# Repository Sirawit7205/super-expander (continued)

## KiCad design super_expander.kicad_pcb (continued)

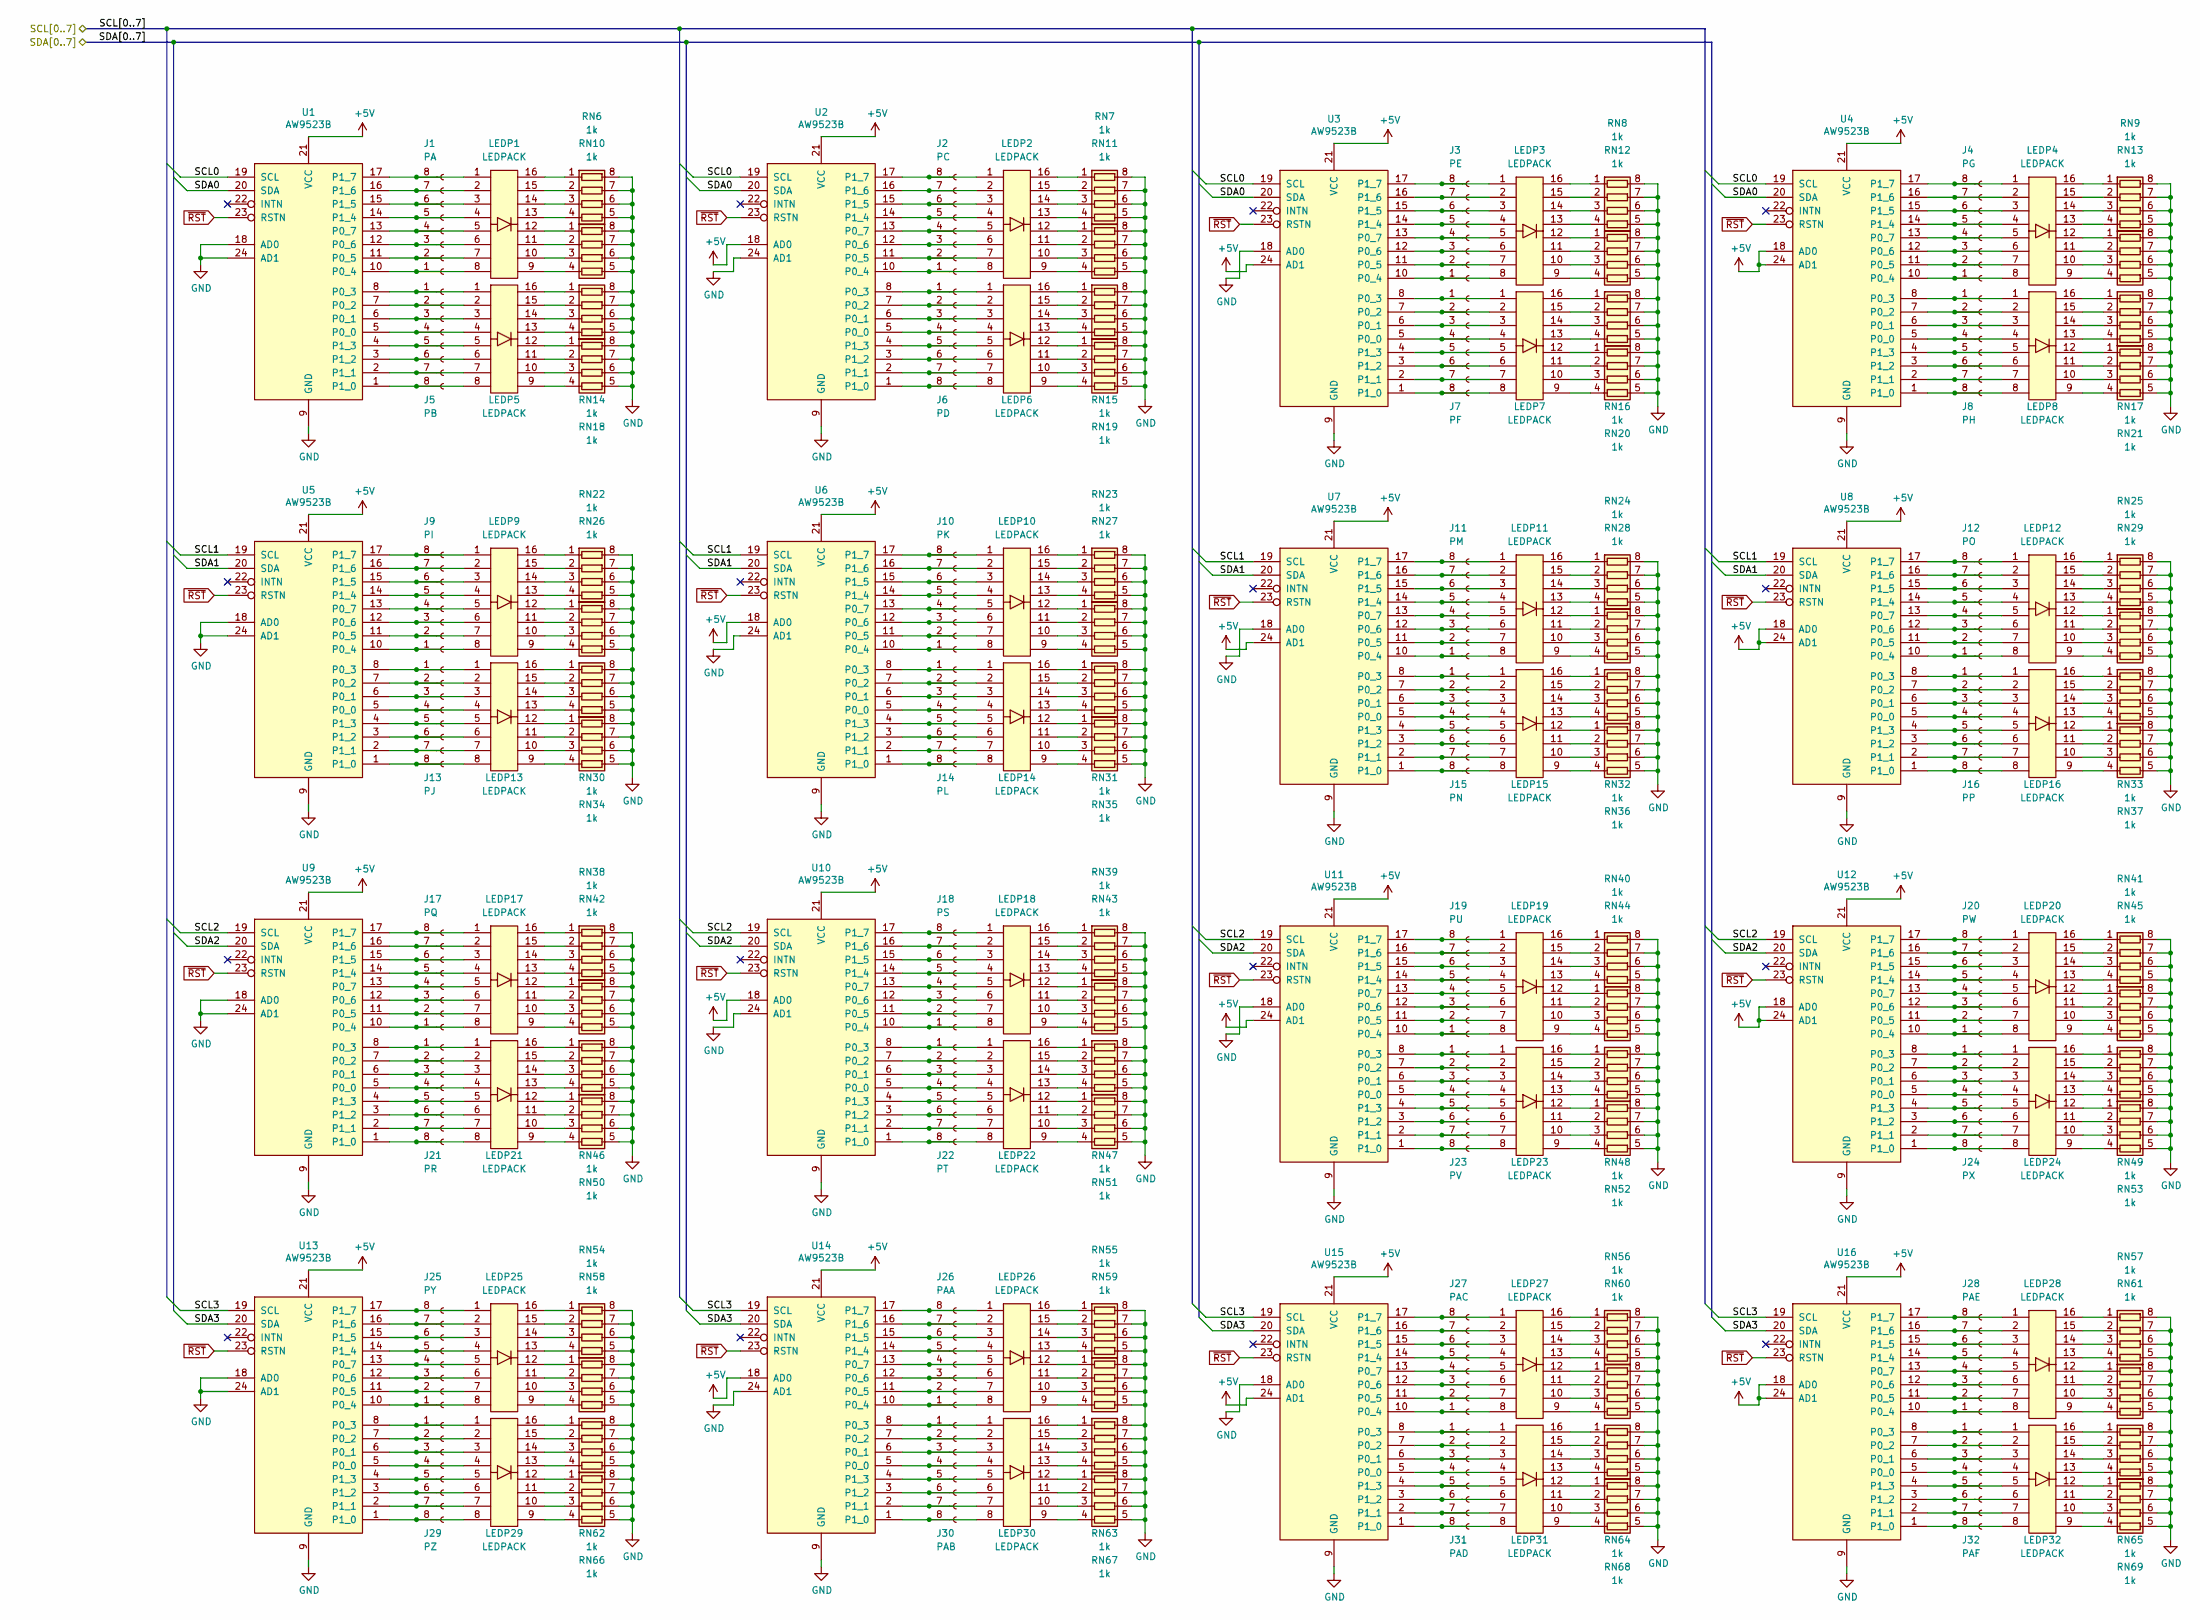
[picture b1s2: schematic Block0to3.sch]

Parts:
J1: PA; PinHeader_1x08_P1.27mm_Vertical
J2: PC; PinHeader_1x08_P1.27mm_Vertical
J3: PE; PinHeader_1x08_P1.27mm_Vertical
J4: PG; PinHeader_1x08_P1.27mm_Vertical
J5: PB; PinHeader_1x08_P1.27mm_Vertical
J6: PD; PinHeader_1x08_P1.27mm_Vertical
J7: PF; PinHeader_1x08_P1.27mm_Vertical
J8: PH; PinHeader_1x08_P1.27mm_Vertical
J9: PI; PinHeader_1x08_P1.27mm_Vertical
J10: PK; PinHeader_1x08_P1.27mm_Vertical
J11: PM; PinHeader_1x08_P1.27mm_Vertical
J12: PO; PinHeader_1x08_P1.27mm_Vertical
J13: PJ; PinHeader_1x08_P1.27mm_Vertical
J14: PL; PinHeader_1x08_P1.27mm_Vertical
J15: PN; PinHeader_1x08_P1.27mm_Vertical
J16: PP; PinHeader_1x08_P1.27mm_Vertical
J17: PQ; PinHeader_1x08_P1.27mm_Vertical
J18: PS; PinHeader_1x08_P1.27mm_Vertical
J19: PU; PinHeader_1x08_P1.27mm_Vertical
J20: PW; PinHeader_1x08_P1.27mm_Vertical
J21: PR; PinHeader_1x08_P1.27mm_Vertical
J22: PT; PinHeader_1x08_P1.27mm_Vertical
J23: PV; PinHeader_1x08_P1.27mm_Vertical
J24: PX; PinHeader_1x08_P1.27mm_Vertical
J25: PY; PinHeader_1x08_P1.27mm_Vertical
J26: PAA; PinHeader_1x08_P1.27mm_Vertical
J27: PAC; PinHeader_1x08_P1.27mm_Vertical
J28: PAE; PinHeader_1x08_P1.27mm_Vertical
J29: PZ; PinHeader_1x08_P1.27mm_Vertical
J30: PAB; PinHeader_1x08_P1.27mm_Vertical
J31: PAD; PinHeader_1x08_P1.27mm_Vertical
J32: PAF; PinHeader_1x08_P1.27mm_Vertical
LEDP1, LEDP2, LEDP3, LEDP4, LEDP5, LEDP6, LEDP7, LEDP8, LEDP9, LEDP10, LEDP11, LEDP12, LEDP13, LEDP14, LEDP15, LEDP16, LEDP17, LEDP18, LEDP19, LEDP20, LEDP21, LEDP22, LEDP23, LEDP24, LEDP25, LEDP26, LEDP27, LEDP28, LEDP29, LEDP30, LEDP31, LEDP32: LEDPACK; LED_PACK_8
RN6, RN7, RN8, RN9, RN10, RN11, RN12, RN13, RN14, RN15, RN16, RN17, RN18, RN19, RN20, RN21, RN22, RN23, RN24, RN25, RN26, RN27, RN28, RN29, RN30, RN31, RN32, RN33, RN34, RN35, RN36, RN37, RN38, RN39, RN40, RN41, RN42, RN43, RN44, RN45, RN46, RN47, RN48, RN49, RN50, RN51, RN52, RN53, RN54, RN55, RN56, RN57, RN58, RN59, RN60, RN61, RN62, RN63, RN64, RN65, RN66, RN67, RN68, RN69: 1k; R_Array_Convex_4x0402
U1, U2, U3, U4, U5, U6, U7, U8, U9, U10, U11, U12, U13, U14, U15, U16: AW9523B; QFN-24-1EP_4x4mm_P0.5mm_EP2.7x2.7mm_ThermalVias

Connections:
+5V: U1.21 (VCC), U2.18 (AD0), U2.21 (VCC), U3.21 (VCC), U3.24 (AD1), U4.18 (AD0), U4.21 (VCC), U4.24 (AD1), U5.21 (VCC), U6.18 (AD0), U6.21 (VCC), U7.21 (VCC), U7.24 (AD1), U8.18 (AD0), U8.21 (VCC), U8.24 (AD1), U9.21 (VCC), U10.18 (AD0), U10.21 (VCC), U11.21 (VCC), U11.24 (AD1), U12.18 (AD0), U12.21 (VCC), U12.24 (AD1), U13.21 (VCC), U14.18 (AD0), U14.21 (VCC), U15.21 (VCC), U15.24 (AD1), U16.18 (AD0), U16.21 (VCC), U16.24 (AD1); also elsewhere on the board
/SCL0: U1.19 (SCL), U2.19 (SCL), U3.19 (SCL), U4.19 (SCL); also elsewhere on the board
/SCL1: U5.19 (SCL), U6.19 (SCL), U7.19 (SCL), U8.19 (SCL); also elsewhere on the board
/SCL2: U9.19 (SCL), U10.19 (SCL), U11.19 (SCL), U12.19 (SCL); also elsewhere on the board
/SCL3: U13.19 (SCL), U14.19 (SCL), U15.19 (SCL), U16.19 (SCL); also elsewhere on the board
/SDA0: U1.20 (SDA), U2.20 (SDA), U3.20 (SDA), U4.20 (SDA); also elsewhere on the board
/SDA1: U5.20 (SDA), U6.20 (SDA), U7.20 (SDA), U8.20 (SDA); also elsewhere on the board
/SDA2: U9.20 (SDA), U10.20 (SDA), U11.20 (SDA), U12.20 (SDA); also elsewhere on the board
/SDA3: U13.20 (SDA), U14.20 (SDA), U15.20 (SDA), U16.20 (SDA); also elsewhere on the board
GND: RN6.5 (R4.2), RN6.6 (R3.2), RN6.7 (R2.2), RN6.8 (R1.2), RN7.5 (R4.2), RN7.6 (R3.2), RN7.7 (R2.2), RN7.8 (R1.2), RN8.5 (R4.2), RN8.6 (R3.2), RN8.7 (R2.2), RN8.8 (R1.2), RN9.5 (R4.2), RN9.6 (R3.2), RN9.7 (R2.2), RN9.8 (R1.2), RN10.5 (R4.2), RN10.6 (R3.2), RN10.7 (R2.2), RN10.8 (R1.2), RN11.5 (R4.2), RN11.6 (R3.2), RN11.7 (R2.2), RN11.8 (R1.2), RN12.5 (R4.2), RN12.6 (R3.2), RN12.7 (R2.2), RN12.8 (R1.2), RN13.5 (R4.2), RN13.6 (R3.2), RN13.7 (R2.2), RN13.8 (R1.2), RN14.5 (R4.2), RN14.6 (R3.2), RN14.7 (R2.2), RN14.8 (R1.2), RN15.5 (R4.2), RN15.6 (R3.2), RN15.7 (R2.2), RN15.8 (R1.2), RN16.5 (R4.2), RN16.6 (R3.2), RN16.7 (R2.2), RN16.8 (R1.2), RN17.5 (R4.2), RN17.6 (R3.2), RN17.7 (R2.2), RN17.8 (R1.2), RN18.5 (R4.2), RN18.6 (R3.2), RN18.7 (R2.2), RN18.8 (R1.2), RN19.5 (R4.2), RN19.6 (R3.2), RN19.7 (R2.2), RN19.8 (R1.2), RN20.5 (R4.2), RN20.6 (R3.2), RN20.7 (R2.2), RN20.8 (R1.2), RN21.5 (R4.2), RN21.6 (R3.2), RN21.7 (R2.2), RN21.8 (R1.2), RN22.5 (R4.2), RN22.6 (R3.2), RN22.7 (R2.2), RN22.8 (R1.2), RN23.5 (R4.2), RN23.6 (R3.2), RN23.7 (R2.2), RN23.8 (R1.2), RN24.5 (R4.2), RN24.6 (R3.2), RN24.7 (R2.2), RN24.8 (R1.2), RN25.5 (R4.2), RN25.6 (R3.2), RN25.7 (R2.2), RN25.8 (R1.2), RN26.5 (R4.2), RN26.6 (R3.2), RN26.7 (R2.2), RN26.8 (R1.2), RN27.5 (R4.2), RN27.6 (R3.2), RN27.7 (R2.2), RN27.8 (R1.2), RN28.5 (R4.2), RN28.6 (R3.2), RN28.7 (R2.2), RN28.8 (R1.2), RN29.5 (R4.2), RN29.6 (R3.2), RN29.7 (R2.2), RN29.8 (R1.2), RN30.5 (R4.2), RN30.6 (R3.2), RN30.7 (R2.2), RN30.8 (R1.2), RN31.5 (R4.2), RN31.6 (R3.2), RN31.7 (R2.2), RN31.8 (R1.2), RN32.5 (R4.2), RN32.6 (R3.2), RN32.7 (R2.2), RN32.8 (R1.2), RN33.5 (R4.2), RN33.6 (R3.2), RN33.7 (R2.2), RN33.8 (R1.2), RN34.5 (R4.2), RN34.6 (R3.2), RN34.7 (R2.2), RN34.8 (R1.2), RN35.5 (R4.2), RN35.6 (R3.2), RN35.7 (R2.2), RN35.8 (R1.2), RN36.5 (R4.2), RN36.6 (R3.2), RN36.7 (R2.2), RN36.8 (R1.2), RN37.5 (R4.2), RN37.6 (R3.2), RN37.7 (R2.2), RN37.8 (R1.2), RN38.5 (R4.2), RN38.6 (R3.2), RN38.7 (R2.2), RN38.8 (R1.2), RN39.5 (R4.2), RN39.6 (R3.2), RN39.7 (R2.2), RN39.8 (R1.2), RN40.5 (R4.2), RN40.6 (R3.2), RN40.7 (R2.2), RN40.8 (R1.2), RN41.5 (R4.2), RN41.6 (R3.2), RN41.7 (R2.2), RN41.8 (R1.2), RN42.5 (R4.2), RN42.6 (R3.2), RN42.7 (R2.2), RN42.8 (R1.2), RN43.5 (R4.2), RN43.6 (R3.2), RN43.7 (R2.2), RN43.8 (R1.2), RN44.5 (R4.2), RN44.6 (R3.2), RN44.7 (R2.2), RN44.8 (R1.2), RN45.5 (R4.2), RN45.6 (R3.2), RN45.7 (R2.2), RN45.8 (R1.2), RN46.5 (R4.2), RN46.6 (R3.2), RN46.7 (R2.2), RN46.8 (R1.2), RN47.5 (R4.2), RN47.6 (R3.2), RN47.7 (R2.2), RN47.8 (R1.2), RN48.5 (R4.2), RN48.6 (R3.2), RN48.7 (R2.2), RN48.8 (R1.2), RN49.5 (R4.2), RN49.6 (R3.2), RN49.7 (R2.2), RN49.8 (R1.2), RN50.5 (R4.2), RN50.6 (R3.2), RN50.7 (R2.2), RN50.8 (R1.2), RN51.5 (R4.2), RN51.6 (R3.2), RN51.7 (R2.2), RN51.8 (R1.2), RN52.5 (R4.2), RN52.6 (R3.2), RN52.7 (R2.2), RN52.8 (R1.2), RN53.5 (R4.2), RN53.6 (R3.2), RN53.7 (R2.2), RN53.8 (R1.2), RN54.5 (R4.2), RN54.6 (R3.2), RN54.7 (R2.2), RN54.8 (R1.2), RN55.5 (R4.2), RN55.6 (R3.2), RN55.7 (R2.2), RN55.8 (R1.2), RN56.5 (R4.2), RN56.6 (R3.2), RN56.7 (R2.2), RN56.8 (R1.2), RN57.5 (R4.2), RN57.6 (R3.2), RN57.7 (R2.2), RN57.8 (R1.2), RN58.5 (R4.2), RN58.6 (R3.2), RN58.7 (R2.2), RN58.8 (R1.2), RN59.5 (R4.2), RN59.6 (R3.2), RN59.7 (R2.2), RN59.8 (R1.2), RN60.5 (R4.2), RN60.6 (R3.2), RN60.7 (R2.2), RN60.8 (R1.2), RN61.5 (R4.2), RN61.6 (R3.2), RN61.7 (R2.2), RN61.8 (R1.2), RN62.5 (R4.2), RN62.6 (R3.2), RN62.7 (R2.2), RN62.8 (R1.2), RN63.5 (R4.2), RN63.6 (R3.2), RN63.7 (R2.2), RN63.8 (R1.2), RN64.5 (R4.2), RN64.6 (R3.2), RN64.7 (R2.2), RN64.8 (R1.2), RN65.5 (R4.2), RN65.6 (R3.2), RN65.7 (R2.2), RN65.8 (R1.2), RN66.5 (R4.2), RN66.6 (R3.2), RN66.7 (R2.2), RN66.8 (R1.2), RN67.5 (R4.2), RN67.6 (R3.2), RN67.7 (R2.2), RN67.8 (R1.2), RN68.5 (R4.2), RN68.6 (R3.2), RN68.7 (R2.2), RN68.8 (R1.2), RN69.5 (R4.2), RN69.6 (R3.2), RN69.7 (R2.2), RN69.8 (R1.2), U1.9 (GND), U1.18 (AD0), U1.24 (AD1), U1.25 (GND), U2.9 (GND), U2.24 (AD1), U2.25 (GND), U3.9 (GND), U3.18 (AD0), U3.25 (GND), U4.9 (GND), U4.25 (GND), U5.9 (GND), U5.18 (AD0), U5.24 (AD1), U5.25 (GND), U6.9 (GND), U6.24 (AD1), U6.25 (GND), U7.9 (GND), U7.18 (AD0), U7.25 (GND), U8.9 (GND), U8.25 (GND), U9.9 (GND), U9.18 (AD0), U9.24 (AD1), U9.25 (GND), U10.9 (GND), U10.24 (AD1), U10.25 (GND), U11.9 (GND), U11.18 (AD0), U11.25 (GND), U12.9 (GND), U12.25 (GND), U13.9 (GND), U13.18 (AD0), U13.24 (AD1), U13.25 (GND), U14.9 (GND), U14.24 (AD1), U14.25 (GND), U15.9 (GND), U15.18 (AD0), U15.25 (GND), U16.9 (GND), U16.25 (GND); also elsewhere on the board
unnamed: J1.1, LEDP1.8, U1.10 (P0_4)
unnamed: J1.2, LEDP1.7, U1.11 (P0_5)
unnamed: J1.3, LEDP1.6, U1.12 (P0_6)
unnamed: J1.4, LEDP1.5, U1.13 (P0_7)
unnamed: J1.5, LEDP1.4, U1.14 (P1_4)
unnamed: J1.6, LEDP1.3, U1.15 (P1_5)
unnamed: J1.7, LEDP1.2, U1.16 (P1_6)
unnamed: J1.8, LEDP1.1, U1.17 (P1_7)
unnamed: J2.1, LEDP2.8, U2.10 (P0_4)
unnamed: J2.2, LEDP2.7, U2.11 (P0_5)
unnamed: J2.3, LEDP2.6, U2.12 (P0_6)
unnamed: J2.4, LEDP2.5, U2.13 (P0_7)
unnamed: J2.5, LEDP2.4, U2.14 (P1_4)
unnamed: J2.6, LEDP2.3, U2.15 (P1_5)
unnamed: J2.7, LEDP2.2, U2.16 (P1_6)
unnamed: J2.8, LEDP2.1, U2.17 (P1_7)
unnamed: J3.1, LEDP3.8, U3.10 (P0_4)
unnamed: J3.2, LEDP3.7, U3.11 (P0_5)
unnamed: J3.3, LEDP3.6, U3.12 (P0_6)
unnamed: J3.4, LEDP3.5, U3.13 (P0_7)
unnamed: J3.5, LEDP3.4, U3.14 (P1_4)
unnamed: J3.6, LEDP3.3, U3.15 (P1_5)
unnamed: J3.7, LEDP3.2, U3.16 (P1_6)
unnamed: J3.8, LEDP3.1, U3.17 (P1_7)
unnamed: J4.1, LEDP4.8, U4.10 (P0_4)
unnamed: J4.2, LEDP4.7, U4.11 (P0_5)
unnamed: J4.3, LEDP4.6, U4.12 (P0_6)
unnamed: J4.4, LEDP4.5, U4.13 (P0_7)
unnamed: J4.5, LEDP4.4, U4.14 (P1_4)
unnamed: J4.6, LEDP4.3, U4.15 (P1_5)
unnamed: J4.7, LEDP4.2, U4.16 (P1_6)
unnamed: J4.8, LEDP4.1, U4.17 (P1_7)
unnamed: J5.1, LEDP5.1, U1.8 (P0_3)
unnamed: J5.2, LEDP5.2, U1.7 (P0_2)
unnamed: J5.3, LEDP5.3, U1.6 (P0_1)
unnamed: J5.4, LEDP5.4, U1.5 (P0_0)
unnamed: J5.5, LEDP5.5, U1.4 (P1_3)
unnamed: J5.6, LEDP5.6, U1.3 (P1_2)
unnamed: J5.7, LEDP5.7, U1.2 (P1_1)
unnamed: J5.8, LEDP5.8, U1.1 (P1_0)
unnamed: J6.1, LEDP6.1, U2.8 (P0_3)
unnamed: J6.2, LEDP6.2, U2.7 (P0_2)
unnamed: J6.3, LEDP6.3, U2.6 (P0_1)
unnamed: J6.4, LEDP6.4, U2.5 (P0_0)
unnamed: J6.5, LEDP6.5, U2.4 (P1_3)
unnamed: J6.6, LEDP6.6, U2.3 (P1_2)
unnamed: J6.7, LEDP6.7, U2.2 (P1_1)
unnamed: J6.8, LEDP6.8, U2.1 (P1_0)
unnamed: J7.1, LEDP7.1, U3.8 (P0_3)
unnamed: J7.2, LEDP7.2, U3.7 (P0_2)
unnamed: J7.3, LEDP7.3, U3.6 (P0_1)
unnamed: J7.4, LEDP7.4, U3.5 (P0_0)
unnamed: J7.5, LEDP7.5, U3.4 (P1_3)
unnamed: J7.6, LEDP7.6, U3.3 (P1_2)
unnamed: J7.7, LEDP7.7, U3.2 (P1_1)
unnamed: J7.8, LEDP7.8, U3.1 (P1_0)
unnamed: J8.1, LEDP8.1, U4.8 (P0_3)
unnamed: J8.2, LEDP8.2, U4.7 (P0_2)
unnamed: J8.3, LEDP8.3, U4.6 (P0_1)
unnamed: J8.4, LEDP8.4, U4.5 (P0_0)
unnamed: J8.5, LEDP8.5, U4.4 (P1_3)
unnamed: J8.6, LEDP8.6, U4.3 (P1_2)
unnamed: J8.7, LEDP8.7, U4.2 (P1_1)
unnamed: J8.8, LEDP8.8, U4.1 (P1_0)
unnamed: J9.1, LEDP9.8, U5.10 (P0_4)
unnamed: J9.2, LEDP9.7, U5.11 (P0_5)
unnamed: J9.3, LEDP9.6, U5.12 (P0_6)
unnamed: J9.4, LEDP9.5, U5.13 (P0_7)
unnamed: J9.5, LEDP9.4, U5.14 (P1_4)
unnamed: J9.6, LEDP9.3, U5.15 (P1_5)
unnamed: J9.7, LEDP9.2, U5.16 (P1_6)
unnamed: J9.8, LEDP9.1, U5.17 (P1_7)
unnamed: J10.1, LEDP10.8, U6.10 (P0_4)
unnamed: J10.2, LEDP10.7, U6.11 (P0_5)
unnamed: J10.3, LEDP10.6, U6.12 (P0_6)
unnamed: J10.4, LEDP10.5, U6.13 (P0_7)
unnamed: J10.5, LEDP10.4, U6.14 (P1_4)
unnamed: J10.6, LEDP10.3, U6.15 (P1_5)
unnamed: J10.7, LEDP10.2, U6.16 (P1_6)
unnamed: J10.8, LEDP10.1, U6.17 (P1_7)
unnamed: J11.1, LEDP11.8, U7.10 (P0_4)
unnamed: J11.2, LEDP11.7, U7.11 (P0_5)
unnamed: J11.3, LEDP11.6, U7.12 (P0_6)
unnamed: J11.4, LEDP11.5, U7.13 (P0_7)
unnamed: J11.5, LEDP11.4, U7.14 (P1_4)
unnamed: J11.6, LEDP11.3, U7.15 (P1_5)
unnamed: J11.7, LEDP11.2, U7.16 (P1_6)
unnamed: J11.8, LEDP11.1, U7.17 (P1_7)
unnamed: J12.1, LEDP12.8, U8.10 (P0_4)
unnamed: J12.2, LEDP12.7, U8.11 (P0_5)
unnamed: J12.3, LEDP12.6, U8.12 (P0_6)
unnamed: J12.4, LEDP12.5, U8.13 (P0_7)
unnamed: J12.5, LEDP12.4, U8.14 (P1_4)
unnamed: J12.6, LEDP12.3, U8.15 (P1_5)
unnamed: J12.7, LEDP12.2, U8.16 (P1_6)
unnamed: J12.8, LEDP12.1, U8.17 (P1_7)
unnamed: J13.1, LEDP13.1, U5.8 (P0_3)
unnamed: J13.2, LEDP13.2, U5.7 (P0_2)
unnamed: J13.3, LEDP13.3, U5.6 (P0_1)
unnamed: J13.4, LEDP13.4, U5.5 (P0_0)
unnamed: J13.5, LEDP13.5, U5.4 (P1_3)
unnamed: J13.6, LEDP13.6, U5.3 (P1_2)
unnamed: J13.7, LEDP13.7, U5.2 (P1_1)
unnamed: J13.8, LEDP13.8, U5.1 (P1_0)
unnamed: J14.1, LEDP14.1, U6.8 (P0_3)
unnamed: J14.2, LEDP14.2, U6.7 (P0_2)
unnamed: J14.3, LEDP14.3, U6.6 (P0_1)
unnamed: J14.4, LEDP14.4, U6.5 (P0_0)
unnamed: J14.5, LEDP14.5, U6.4 (P1_3)
unnamed: J14.6, LEDP14.6, U6.3 (P1_2)
unnamed: J14.7, LEDP14.7, U6.2 (P1_1)
unnamed: J14.8, LEDP14.8, U6.1 (P1_0)
unnamed: J15.1, LEDP15.1, U7.8 (P0_3)
unnamed: J15.2, LEDP15.2, U7.7 (P0_2)
unnamed: J15.3, LEDP15.3, U7.6 (P0_1)
unnamed: J15.4, LEDP15.4, U7.5 (P0_0)
unnamed: J15.5, LEDP15.5, U7.4 (P1_3)
unnamed: J15.6, LEDP15.6, U7.3 (P1_2)
unnamed: J15.7, LEDP15.7, U7.2 (P1_1)
unnamed: J15.8, LEDP15.8, U7.1 (P1_0)
unnamed: J16.1, LEDP16.1, U8.8 (P0_3)
unnamed: J16.2, LEDP16.2, U8.7 (P0_2)
unnamed: J16.3, LEDP16.3, U8.6 (P0_1)
unnamed: J16.4, LEDP16.4, U8.5 (P0_0)
unnamed: J16.5, LEDP16.5, U8.4 (P1_3)
unnamed: J16.6, LEDP16.6, U8.3 (P1_2)
unnamed: J16.7, LEDP16.7, U8.2 (P1_1)
unnamed: J16.8, LEDP16.8, U8.1 (P1_0)
unnamed: J17.1, LEDP17.8, U9.10 (P0_4)
unnamed: J17.2, LEDP17.7, U9.11 (P0_5)
unnamed: J17.3, LEDP17.6, U9.12 (P0_6)
unnamed: J17.4, LEDP17.5, U9.13 (P0_7)
unnamed: J17.5, LEDP17.4, U9.14 (P1_4)
unnamed: J17.6, LEDP17.3, U9.15 (P1_5)
unnamed: J17.7, LEDP17.2, U9.16 (P1_6)
unnamed: J17.8, LEDP17.1, U9.17 (P1_7)
unnamed: J18.1, LEDP18.8, U10.10 (P0_4)
unnamed: J18.2, LEDP18.7, U10.11 (P0_5)
unnamed: J18.3, LEDP18.6, U10.12 (P0_6)
unnamed: J18.4, LEDP18.5, U10.13 (P0_7)
unnamed: J18.5, LEDP18.4, U10.14 (P1_4)
unnamed: J18.6, LEDP18.3, U10.15 (P1_5)
unnamed: J18.7, LEDP18.2, U10.16 (P1_6)
unnamed: J18.8, LEDP18.1, U10.17 (P1_7)
unnamed: J19.1, LEDP19.8, U11.10 (P0_4)
unnamed: J19.2, LEDP19.7, U11.11 (P0_5)
unnamed: J19.3, LEDP19.6, U11.12 (P0_6)
unnamed: J19.4, LEDP19.5, U11.13 (P0_7)
unnamed: J19.5, LEDP19.4, U11.14 (P1_4)
unnamed: J19.6, LEDP19.3, U11.15 (P1_5)
unnamed: J19.7, LEDP19.2, U11.16 (P1_6)
unnamed: J19.8, LEDP19.1, U11.17 (P1_7)
unnamed: J20.1, LEDP20.8, U12.10 (P0_4)
unnamed: J20.2, LEDP20.7, U12.11 (P0_5)
unnamed: J20.3, LEDP20.6, U12.12 (P0_6)
unnamed: J20.4, LEDP20.5, U12.13 (P0_7)
unnamed: J20.5, LEDP20.4, U12.14 (P1_4)
unnamed: J20.6, LEDP20.3, U12.15 (P1_5)
unnamed: J20.7, LEDP20.2, U12.16 (P1_6)
unnamed: J20.8, LEDP20.1, U12.17 (P1_7)
unnamed: J21.1, LEDP21.1, U9.8 (P0_3)
unnamed: J21.2, LEDP21.2, U9.7 (P0_2)
unnamed: J21.3, LEDP21.3, U9.6 (P0_1)
unnamed: J21.4, LEDP21.4, U9.5 (P0_0)
unnamed: J21.5, LEDP21.5, U9.4 (P1_3)
unnamed: J21.6, LEDP21.6, U9.3 (P1_2)
unnamed: J21.7, LEDP21.7, U9.2 (P1_1)
unnamed: J21.8, LEDP21.8, U9.1 (P1_0)
unnamed: J22.1, LEDP22.1, U10.8 (P0_3)
unnamed: J22.2, LEDP22.2, U10.7 (P0_2)
unnamed: J22.3, LEDP22.3, U10.6 (P0_1)
unnamed: J22.4, LEDP22.4, U10.5 (P0_0)
unnamed: J22.5, LEDP22.5, U10.4 (P1_3)
unnamed: J22.6, LEDP22.6, U10.3 (P1_2)
unnamed: J22.7, LEDP22.7, U10.2 (P1_1)
unnamed: J22.8, LEDP22.8, U10.1 (P1_0)
unnamed: J23.1, LEDP23.1, U11.8 (P0_3)
unnamed: J23.2, LEDP23.2, U11.7 (P0_2)
unnamed: J23.3, LEDP23.3, U11.6 (P0_1)
unnamed: J23.4, LEDP23.4, U11.5 (P0_0)
unnamed: J23.5, LEDP23.5, U11.4 (P1_3)
unnamed: J23.6, LEDP23.6, U11.3 (P1_2)
unnamed: J23.7, LEDP23.7, U11.2 (P1_1)
unnamed: J23.8, LEDP23.8, U11.1 (P1_0)
unnamed: J24.1, LEDP24.1, U12.8 (P0_3)
unnamed: J24.2, LEDP24.2, U12.7 (P0_2)
unnamed: J24.3, LEDP24.3, U12.6 (P0_1)
unnamed: J24.4, LEDP24.4, U12.5 (P0_0)
unnamed: J24.5, LEDP24.5, U12.4 (P1_3)
unnamed: J24.6, LEDP24.6, U12.3 (P1_2)
unnamed: J24.7, LEDP24.7, U12.2 (P1_1)
unnamed: J24.8, LEDP24.8, U12.1 (P1_0)
unnamed: J25.1, LEDP25.8, U13.10 (P0_4)
unnamed: J25.2, LEDP25.7, U13.11 (P0_5)
unnamed: J25.3, LEDP25.6, U13.12 (P0_6)
unnamed: J25.4, LEDP25.5, U13.13 (P0_7)
unnamed: J25.5, LEDP25.4, U13.14 (P1_4)
unnamed: J25.6, LEDP25.3, U13.15 (P1_5)
unnamed: J25.7, LEDP25.2, U13.16 (P1_6)
unnamed: J25.8, LEDP25.1, U13.17 (P1_7)
unnamed: J26.1, LEDP26.8, U14.10 (P0_4)
unnamed: J26.2, LEDP26.7, U14.11 (P0_5)
unnamed: J26.3, LEDP26.6, U14.12 (P0_6)
unnamed: J26.4, LEDP26.5, U14.13 (P0_7)
unnamed: J26.5, LEDP26.4, U14.14 (P1_4)
unnamed: J26.6, LEDP26.3, U14.15 (P1_5)
unnamed: J26.7, LEDP26.2, U14.16 (P1_6)
unnamed: J26.8, LEDP26.1, U14.17 (P1_7)
unnamed: J27.1, LEDP27.8, U15.10 (P0_4)
unnamed: J27.2, LEDP27.7, U15.11 (P0_5)
unnamed: J27.3, LEDP27.6, U15.12 (P0_6)
unnamed: J27.4, LEDP27.5, U15.13 (P0_7)
unnamed: J27.5, LEDP27.4, U15.14 (P1_4)
unnamed: J27.6, LEDP27.3, U15.15 (P1_5)
unnamed: J27.7, LEDP27.2, U15.16 (P1_6)
unnamed: J27.8, LEDP27.1, U15.17 (P1_7)
unnamed: J28.1, LEDP28.8, U16.10 (P0_4)
unnamed: J28.2, LEDP28.7, U16.11 (P0_5)
unnamed: J28.3, LEDP28.6, U16.12 (P0_6)
unnamed: J28.4, LEDP28.5, U16.13 (P0_7)
unnamed: J28.5, LEDP28.4, U16.14 (P1_4)
unnamed: J28.6, LEDP28.3, U16.15 (P1_5)
unnamed: J28.7, LEDP28.2, U16.16 (P1_6)
unnamed: J28.8, LEDP28.1, U16.17 (P1_7)
unnamed: J29.1, LEDP29.1, U13.8 (P0_3)
unnamed: J29.2, LEDP29.2, U13.7 (P0_2)
unnamed: J29.3, LEDP29.3, U13.6 (P0_1)
unnamed: J29.4, LEDP29.4, U13.5 (P0_0)
unnamed: J29.5, LEDP29.5, U13.4 (P1_3)
unnamed: J29.6, LEDP29.6, U13.3 (P1_2)
unnamed: J29.7, LEDP29.7, U13.2 (P1_1)
unnamed: J29.8, LEDP29.8, U13.1 (P1_0)
unnamed: J30.1, LEDP30.1, U14.8 (P0_3)
unnamed: J30.2, LEDP30.2, U14.7 (P0_2)
unnamed: J30.3, LEDP30.3, U14.6 (P0_1)
unnamed: J30.4, LEDP30.4, U14.5 (P0_0)
unnamed: J30.5, LEDP30.5, U14.4 (P1_3)
unnamed: J30.6, LEDP30.6, U14.3 (P1_2)
unnamed: J30.7, LEDP30.7, U14.2 (P1_1)
unnamed: J30.8, LEDP30.8, U14.1 (P1_0)
unnamed: J31.1, LEDP31.1, U15.8 (P0_3)
unnamed: J31.2, LEDP31.2, U15.7 (P0_2)
unnamed: J31.3, LEDP31.3, U15.6 (P0_1)
unnamed: J31.4, LEDP31.4, U15.5 (P0_0)
unnamed: J31.5, LEDP31.5, U15.4 (P1_3)
unnamed: J31.6, LEDP31.6, U15.3 (P1_2)
unnamed: J31.7, LEDP31.7, U15.2 (P1_1)
unnamed: J31.8, LEDP31.8, U15.1 (P1_0)
unnamed: J32.1, LEDP32.1, U16.8 (P0_3)
unnamed: J32.2, LEDP32.2, U16.7 (P0_2)
unnamed: J32.3, LEDP32.3, U16.6 (P0_1)
unnamed: J32.4, LEDP32.4, U16.5 (P0_0)
unnamed: J32.5, LEDP32.5, U16.4 (P1_3)
unnamed: J32.6, LEDP32.6, U16.3 (P1_2)
unnamed: J32.7, LEDP32.7, U16.2 (P1_1)
unnamed: J32.8, LEDP32.8, U16.1 (P1_0)
unnamed: LEDP1.9, RN10.4 (R4.1)
unnamed: LEDP1.10, RN10.3 (R3.1)
unnamed: LEDP1.11, RN10.2 (R2.1)
unnamed: LEDP1.12, RN10.1 (R1.1)
unnamed: LEDP1.13, RN6.4 (R4.1)
unnamed: LEDP1.14, RN6.3 (R3.1)
unnamed: LEDP1.15, RN6.2 (R2.1)
unnamed: LEDP1.16, RN6.1 (R1.1)
unnamed: LEDP2.9, RN11.4 (R4.1)
unnamed: LEDP2.10, RN11.3 (R3.1)
unnamed: LEDP2.11, RN11.2 (R2.1)
unnamed: LEDP2.12, RN11.1 (R1.1)
unnamed: LEDP2.13, RN7.4 (R4.1)
unnamed: LEDP2.14, RN7.3 (R3.1)
unnamed: LEDP2.15, RN7.2 (R2.1)
unnamed: LEDP2.16, RN7.1 (R1.1)
unnamed: LEDP3.9, RN12.4 (R4.1)
unnamed: LEDP3.10, RN12.3 (R3.1)
unnamed: LEDP3.11, RN12.2 (R2.1)
unnamed: LEDP3.12, RN12.1 (R1.1)
unnamed: LEDP3.13, RN8.4 (R4.1)
unnamed: LEDP3.14, RN8.3 (R3.1)
unnamed: LEDP3.15, RN8.2 (R2.1)
unnamed: LEDP3.16, RN8.1 (R1.1)
unnamed: LEDP4.9, RN13.4 (R4.1)
unnamed: LEDP4.10, RN13.3 (R3.1)
unnamed: LEDP4.11, RN13.2 (R2.1)
unnamed: LEDP4.12, RN13.1 (R1.1)
unnamed: LEDP4.13, RN9.4 (R4.1)
unnamed: LEDP4.14, RN9.3 (R3.1)
unnamed: LEDP4.15, RN9.2 (R2.1)
unnamed: LEDP4.16, RN9.1 (R1.1)
unnamed: LEDP5.9, RN18.4 (R4.1)
unnamed: LEDP5.10, RN18.3 (R3.1)
unnamed: LEDP5.11, RN18.2 (R2.1)
unnamed: LEDP5.12, RN18.1 (R1.1)
unnamed: LEDP5.13, RN14.4 (R4.1)
unnamed: LEDP5.14, RN14.3 (R3.1)
unnamed: LEDP5.15, RN14.2 (R2.1)
unnamed: LEDP5.16, RN14.1 (R1.1)
unnamed: LEDP6.9, RN19.4 (R4.1)
unnamed: LEDP6.10, RN19.3 (R3.1)
unnamed: LEDP6.11, RN19.2 (R2.1)
unnamed: LEDP6.12, RN19.1 (R1.1)
unnamed: LEDP6.13, RN15.4 (R4.1)
unnamed: LEDP6.14, RN15.3 (R3.1)
unnamed: LEDP6.15, RN15.2 (R2.1)
unnamed: LEDP6.16, RN15.1 (R1.1)
unnamed: LEDP7.9, RN20.4 (R4.1)
unnamed: LEDP7.10, RN20.3 (R3.1)
unnamed: LEDP7.11, RN20.2 (R2.1)
unnamed: LEDP7.12, RN20.1 (R1.1)
unnamed: LEDP7.13, RN16.4 (R4.1)
unnamed: LEDP7.14, RN16.3 (R3.1)
unnamed: LEDP7.15, RN16.2 (R2.1)
unnamed: LEDP7.16, RN16.1 (R1.1)
unnamed: LEDP8.9, RN21.4 (R4.1)
unnamed: LEDP8.10, RN21.3 (R3.1)
unnamed: LEDP8.11, RN21.2 (R2.1)
unnamed: LEDP8.12, RN21.1 (R1.1)
unnamed: LEDP8.13, RN17.4 (R4.1)
unnamed: LEDP8.14, RN17.3 (R3.1)
unnamed: LEDP8.15, RN17.2 (R2.1)
unnamed: LEDP8.16, RN17.1 (R1.1)
unnamed: LEDP9.9, RN26.4 (R4.1)
unnamed: LEDP9.10, RN26.3 (R3.1)
unnamed: LEDP9.11, RN26.2 (R2.1)
unnamed: LEDP9.12, RN26.1 (R1.1)
unnamed: LEDP9.13, RN22.4 (R4.1)
unnamed: LEDP9.14, RN22.3 (R3.1)
unnamed: LEDP9.15, RN22.2 (R2.1)
unnamed: LEDP9.16, RN22.1 (R1.1)
unnamed: LEDP10.9, RN27.4 (R4.1)
unnamed: LEDP10.10, RN27.3 (R3.1)
unnamed: LEDP10.11, RN27.2 (R2.1)
unnamed: LEDP10.12, RN27.1 (R1.1)
unnamed: LEDP10.13, RN23.4 (R4.1)
unnamed: LEDP10.14, RN23.3 (R3.1)
unnamed: LEDP10.15, RN23.2 (R2.1)
unnamed: LEDP10.16, RN23.1 (R1.1)
unnamed: LEDP11.9, RN28.4 (R4.1)
unnamed: LEDP11.10, RN28.3 (R3.1)
unnamed: LEDP11.11, RN28.2 (R2.1)
unnamed: LEDP11.12, RN28.1 (R1.1)
unnamed: LEDP11.13, RN24.4 (R4.1)
unnamed: LEDP11.14, RN24.3 (R3.1)
unnamed: LEDP11.15, RN24.2 (R2.1)
unnamed: LEDP11.16, RN24.1 (R1.1)
unnamed: LEDP12.9, RN29.4 (R4.1)
unnamed: LEDP12.10, RN29.3 (R3.1)
unnamed: LEDP12.11, RN29.2 (R2.1)
unnamed: LEDP12.12, RN29.1 (R1.1)
unnamed: LEDP12.13, RN25.4 (R4.1)
unnamed: LEDP12.14, RN25.3 (R3.1)
unnamed: LEDP12.15, RN25.2 (R2.1)
unnamed: LEDP12.16, RN25.1 (R1.1)
unnamed: LEDP13.9, RN34.4 (R4.1)
unnamed: LEDP13.10, RN34.3 (R3.1)
unnamed: LEDP13.11, RN34.2 (R2.1)
unnamed: LEDP13.12, RN34.1 (R1.1)
unnamed: LEDP13.13, RN30.4 (R4.1)
unnamed: LEDP13.14, RN30.3 (R3.1)
unnamed: LEDP13.15, RN30.2 (R2.1)
unnamed: LEDP13.16, RN30.1 (R1.1)
unnamed: LEDP14.9, RN35.4 (R4.1)
unnamed: LEDP14.10, RN35.3 (R3.1)
unnamed: LEDP14.11, RN35.2 (R2.1)
unnamed: LEDP14.12, RN35.1 (R1.1)
unnamed: LEDP14.13, RN31.4 (R4.1)
unnamed: LEDP14.14, RN31.3 (R3.1)
unnamed: LEDP14.15, RN31.2 (R2.1)
unnamed: LEDP14.16, RN31.1 (R1.1)
unnamed: LEDP15.9, RN36.4 (R4.1)
unnamed: LEDP15.10, RN36.3 (R3.1)
unnamed: LEDP15.11, RN36.2 (R2.1)
unnamed: LEDP15.12, RN36.1 (R1.1)
unnamed: LEDP15.13, RN32.4 (R4.1)
unnamed: LEDP15.14, RN32.3 (R3.1)
unnamed: LEDP15.15, RN32.2 (R2.1)
unnamed: LEDP15.16, RN32.1 (R1.1)
unnamed: LEDP16.9, RN37.4 (R4.1)
unnamed: LEDP16.10, RN37.3 (R3.1)
unnamed: LEDP16.11, RN37.2 (R2.1)
unnamed: LEDP16.12, RN37.1 (R1.1)
unnamed: LEDP16.13, RN33.4 (R4.1)
unnamed: LEDP16.14, RN33.3 (R3.1)
unnamed: LEDP16.15, RN33.2 (R2.1)
unnamed: LEDP16.16, RN33.1 (R1.1)
unnamed: LEDP17.9, RN42.4 (R4.1)
unnamed: LEDP17.10, RN42.3 (R3.1)
unnamed: LEDP17.11, RN42.2 (R2.1)
unnamed: LEDP17.12, RN42.1 (R1.1)
unnamed: LEDP17.13, RN38.4 (R4.1)
unnamed: LEDP17.14, RN38.3 (R3.1)
unnamed: LEDP17.15, RN38.2 (R2.1)
unnamed: LEDP17.16, RN38.1 (R1.1)
unnamed: LEDP18.9, RN43.4 (R4.1)
unnamed: LEDP18.10, RN43.3 (R3.1)
unnamed: LEDP18.11, RN43.2 (R2.1)
unnamed: LEDP18.12, RN43.1 (R1.1)
unnamed: LEDP18.13, RN39.4 (R4.1)
unnamed: LEDP18.14, RN39.3 (R3.1)
unnamed: LEDP18.15, RN39.2 (R2.1)
unnamed: LEDP18.16, RN39.1 (R1.1)
unnamed: LEDP19.9, RN44.4 (R4.1)
unnamed: LEDP19.10, RN44.3 (R3.1)
unnamed: LEDP19.11, RN44.2 (R2.1)
unnamed: LEDP19.12, RN44.1 (R1.1)
unnamed: LEDP19.13, RN40.4 (R4.1)
unnamed: LEDP19.14, RN40.3 (R3.1)
unnamed: LEDP19.15, RN40.2 (R2.1)
unnamed: LEDP19.16, RN40.1 (R1.1)
unnamed: LEDP20.9, RN45.4 (R4.1)
unnamed: LEDP20.10, RN45.3 (R3.1)
unnamed: LEDP20.11, RN45.2 (R2.1)
unnamed: LEDP20.12, RN45.1 (R1.1)
unnamed: LEDP20.13, RN41.4 (R4.1)
unnamed: LEDP20.14, RN41.3 (R3.1)
unnamed: LEDP20.15, RN41.2 (R2.1)
unnamed: LEDP20.16, RN41.1 (R1.1)
unnamed: LEDP21.9, RN50.4 (R4.1)
unnamed: LEDP21.10, RN50.3 (R3.1)
unnamed: LEDP21.11, RN50.2 (R2.1)
unnamed: LEDP21.12, RN50.1 (R1.1)
unnamed: LEDP21.13, RN46.4 (R4.1)
unnamed: LEDP21.14, RN46.3 (R3.1)
unnamed: LEDP21.15, RN46.2 (R2.1)
unnamed: LEDP21.16, RN46.1 (R1.1)
unnamed: LEDP22.9, RN51.4 (R4.1)
unnamed: LEDP22.10, RN51.3 (R3.1)
unnamed: LEDP22.11, RN51.2 (R2.1)
unnamed: LEDP22.12, RN51.1 (R1.1)
unnamed: LEDP22.13, RN47.4 (R4.1)
unnamed: LEDP22.14, RN47.3 (R3.1)
unnamed: LEDP22.15, RN47.2 (R2.1)
unnamed: LEDP22.16, RN47.1 (R1.1)
unnamed: LEDP23.9, RN52.4 (R4.1)
unnamed: LEDP23.10, RN52.3 (R3.1)
unnamed: LEDP23.11, RN52.2 (R2.1)
unnamed: LEDP23.12, RN52.1 (R1.1)
unnamed: LEDP23.13, RN48.4 (R4.1)
unnamed: LEDP23.14, RN48.3 (R3.1)
unnamed: LEDP23.15, RN48.2 (R2.1)
unnamed: LEDP23.16, RN48.1 (R1.1)
unnamed: LEDP24.9, RN53.4 (R4.1)
unnamed: LEDP24.10, RN53.3 (R3.1)
unnamed: LEDP24.11, RN53.2 (R2.1)
unnamed: LEDP24.12, RN53.1 (R1.1)
unnamed: LEDP24.13, RN49.4 (R4.1)
unnamed: LEDP24.14, RN49.3 (R3.1)
unnamed: LEDP24.15, RN49.2 (R2.1)
unnamed: LEDP24.16, RN49.1 (R1.1)
unnamed: LEDP25.9, RN58.4 (R4.1)
unnamed: LEDP25.10, RN58.3 (R3.1)
unnamed: LEDP25.11, RN58.2 (R2.1)
unnamed: LEDP25.12, RN58.1 (R1.1)
unnamed: LEDP25.13, RN54.4 (R4.1)
unnamed: LEDP25.14, RN54.3 (R3.1)
unnamed: LEDP25.15, RN54.2 (R2.1)
unnamed: LEDP25.16, RN54.1 (R1.1)
unnamed: LEDP26.9, RN59.4 (R4.1)
unnamed: LEDP26.10, RN59.3 (R3.1)
unnamed: LEDP26.11, RN59.2 (R2.1)
unnamed: LEDP26.12, RN59.1 (R1.1)
unnamed: LEDP26.13, RN55.4 (R4.1)
unnamed: LEDP26.14, RN55.3 (R3.1)
unnamed: LEDP26.15, RN55.2 (R2.1)
unnamed: LEDP26.16, RN55.1 (R1.1)
unnamed: LEDP27.9, RN60.4 (R4.1)
unnamed: LEDP27.10, RN60.3 (R3.1)
unnamed: LEDP27.11, RN60.2 (R2.1)
unnamed: LEDP27.12, RN60.1 (R1.1)
unnamed: LEDP27.13, RN56.4 (R4.1)
unnamed: LEDP27.14, RN56.3 (R3.1)
unnamed: LEDP27.15, RN56.2 (R2.1)
unnamed: LEDP27.16, RN56.1 (R1.1)
unnamed: LEDP28.9, RN61.4 (R4.1)
unnamed: LEDP28.10, RN61.3 (R3.1)
unnamed: LEDP28.11, RN61.2 (R2.1)
unnamed: LEDP28.12, RN61.1 (R1.1)
unnamed: LEDP28.13, RN57.4 (R4.1)
unnamed: LEDP28.14, RN57.3 (R3.1)
unnamed: LEDP28.15, RN57.2 (R2.1)
unnamed: LEDP28.16, RN57.1 (R1.1)
unnamed: LEDP29.9, RN66.4 (R4.1)
unnamed: LEDP29.10, RN66.3 (R3.1)
unnamed: LEDP29.11, RN66.2 (R2.1)
unnamed: LEDP29.12, RN66.1 (R1.1)
unnamed: LEDP29.13, RN62.4 (R4.1)
unnamed: LEDP29.14, RN62.3 (R3.1)
unnamed: LEDP29.15, RN62.2 (R2.1)
unnamed: LEDP29.16, RN62.1 (R1.1)
unnamed: LEDP30.9, RN67.4 (R4.1)
unnamed: LEDP30.10, RN67.3 (R3.1)
unnamed: LEDP30.11, RN67.2 (R2.1)
unnamed: LEDP30.12, RN67.1 (R1.1)
unnamed: LEDP30.13, RN63.4 (R4.1)
unnamed: LEDP30.14, RN63.3 (R3.1)
unnamed: LEDP30.15, RN63.2 (R2.1)
unnamed: LEDP30.16, RN63.1 (R1.1)
unnamed: LEDP31.9, RN68.4 (R4.1)
unnamed: LEDP31.10, RN68.3 (R3.1)
unnamed: LEDP31.11, RN68.2 (R2.1)
unnamed: LEDP31.12, RN68.1 (R1.1)
unnamed: LEDP31.13, RN64.4 (R4.1)
unnamed: LEDP31.14, RN64.3 (R3.1)
unnamed: LEDP31.15, RN64.2 (R2.1)
unnamed: LEDP31.16, RN64.1 (R1.1)
unnamed: LEDP32.9, RN69.4 (R4.1)
unnamed: LEDP32.10, RN69.3 (R3.1)
unnamed: LEDP32.11, RN69.2 (R2.1)
unnamed: LEDP32.12, RN69.1 (R1.1)
unnamed: LEDP32.13, RN65.4 (R4.1)
unnamed: LEDP32.14, RN65.3 (R3.1)
unnamed: LEDP32.15, RN65.2 (R2.1)
unnamed: LEDP32.16, RN65.1 (R1.1)
~RST: U1.23 (RSTN), U2.23 (RSTN), U3.23 (RSTN), U4.23 (RSTN), U5.23 (RSTN), U6.23 (RSTN), U7.23 (RSTN), U8.23 (RSTN), U9.23 (RSTN), U10.23 (RSTN), U11.23 (RSTN), U12.23 (RSTN), U13.23 (RSTN), U14.23 (RSTN), U15.23 (RSTN), U16.23 (RSTN); also elsewhere on the board
